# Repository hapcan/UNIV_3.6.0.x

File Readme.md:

UNIV 3.6.0.x
============

Light Dimmer - 1 channel trailing edge light dimmer 250W for DIN rail

Device webpage: http://hapcan.com/devices/universal/univ_3/univ_3-6-0-x/

Hardware designed in Eagle PCB Software http://www.cadsoftusa.com/

Firmware created in Microchip MPLAB http://www.microchip.com/mplabide/ in assembly language

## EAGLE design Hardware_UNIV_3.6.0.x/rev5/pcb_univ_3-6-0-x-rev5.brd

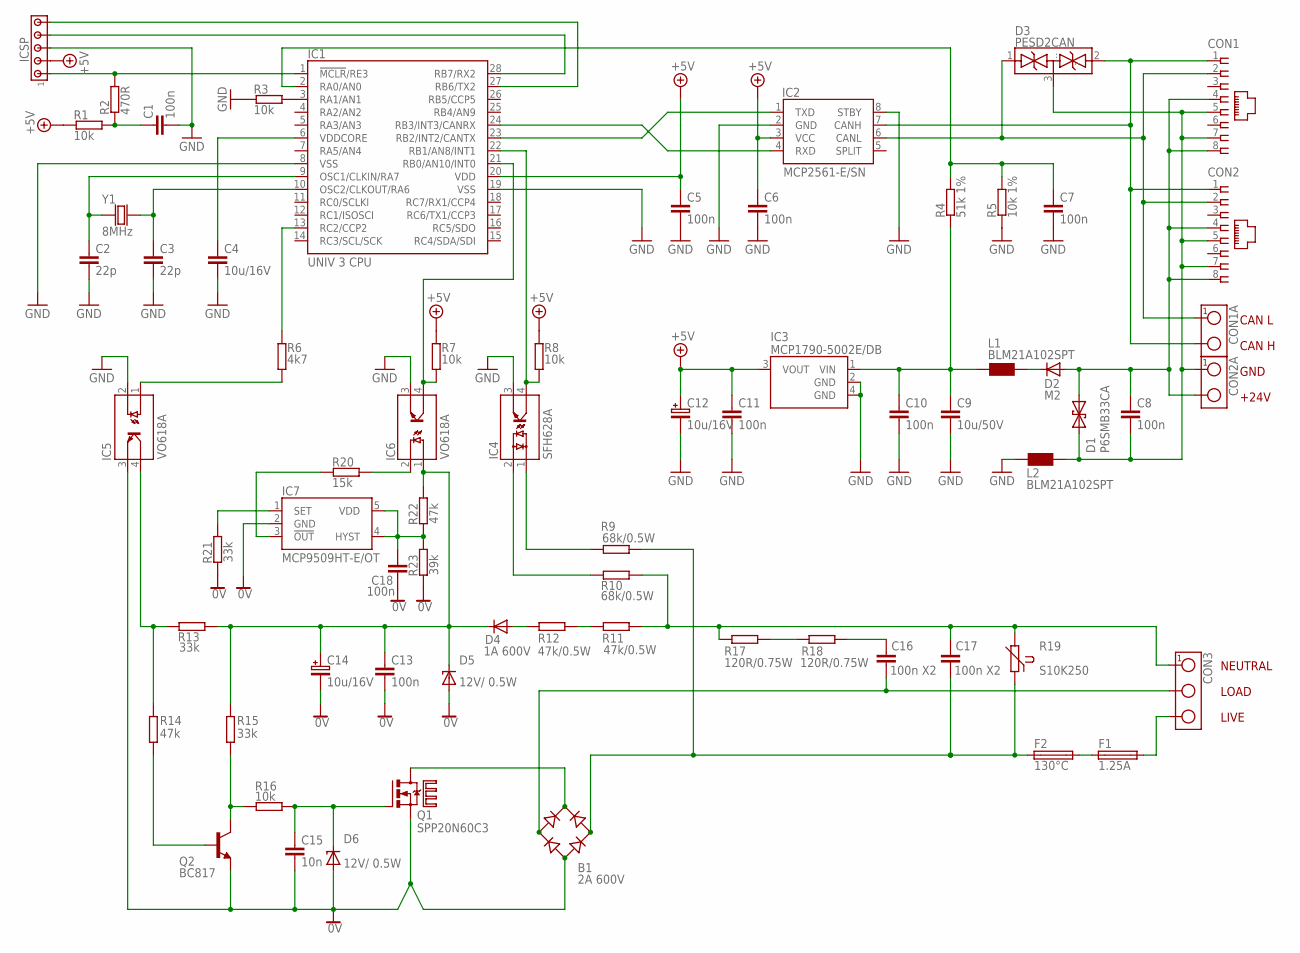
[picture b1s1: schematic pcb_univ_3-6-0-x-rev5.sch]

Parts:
B1: 2A 600V; RECTIFIER_KBP
C1, C5, C6, C7, C8, C10, C11, C13, C18: 100n; 0805
C2, C3: 22p; 0805
C4: 10u/16V; 0805
C9: 10u/50V; 1210
C12, C14: 10u/16V; SMC_B
C15: 10n; 0805
C16, C17: 100n X2; CAP-15X5
CON1, CON2: RJ45-SOCKET; RJ45-PCB-SOCKET
CON1A, CON2A: TERMINAL-2; ARK2-5X10,5MM
CON3: TERMINAL-3; ARK3-5X10.5MM
D1: P6SMB33CA; DO-214_TRANSIL2
D2: M2; DO-214
D3: PESD2CAN; SOT-23
D4: 1A 600V; DO-213
D5, D6: 12V/ 0.5W; SOD-80
F1: 1.25A; FUSE-HOLDER-V
F2: 130°C; FUSE-7.5
IC1: UNIV 3 CPU; UNIV3CPU
IC2: MCP2561-E/SN; SO-08
IC3: MCP1790-5002E/DB; SOT-223
IC4: SFH628A; DIL-04W
IC5, IC6: VO618A; DIL-04W
IC7: MCP9509HT-E/OT; SOT-23-5
ICSP: HEADER5; SIP-5
L1, L2: BLM21A102SPT; 0805
Q1: SPP20N60C3; TO220V-3
Q2: BC817; SOT-23
R1, R3, R7, R8, R16: 10k; 0805
R2: 470R; 0805
R4: 51k 1%; 0805
R5: 10k 1%; 0805
R6: 4k7; 0805
R9, R10: 68k/0.5W; 2010
R11, R12: 47k/0.5W; 2010
R13, R15, R21: 33k; 0805
R14, R22: 47k; 0805
R17, R18: 120R/0.75W; 2010
R19: S10K250; VARISTOR3
R20: 15k; 0805
R23: 39k; 0805
U$1: HEATSINK_HS003; HEATSINK_HS-003
Y1: 8MHz; CRYSTAL-HC49V

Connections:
0V: B1.-, C13.2, C14.- (2), C15.2, C18.2, D5.A, D6.A, IC5.3 (E), IC7.2 (GND), Q1.3 (S), Q2.2 (E), R21.2, R23.2
+5V: C5.1, C6.1, C11.1, C12.+ (1), IC1.20 (VDD), IC2.3 (VCC), IC3.3 (VOUT), ICSP.2, R1.1, R7.2, R8.2
GND: C1.2, C2.2, C3.2, C4.2, C5.2, C6.2, C7.2, C9.2, C10.2, C11.2, C12.- (2), IC1.8 (VSS), IC1.19 (VSS), IC2.2 (GND), IC2.8 (STBY), IC3.2 (GND), IC3.4 (GND), IC4.3 (E1), IC5.2 (K), IC6.3 (E), ICSP.3, L2.1, R3.1, R5.1
unnamed: C13.1, C14.+ (1), D4.C, D5.C, IC6.1 (A), R13.2, R15.1, R22.2
unnamed: IC1.24 (RB3/INT3/CANRX), IC2.4 (RXD)
unnamed: IC1.23 (RB2/INT2/CANTX), IC2.1 (TXD)
unnamed: CON1.1, CON1A.2, CON2.1, D3.2 (..), IC2.7 (CANH)
unnamed: IC4.2 (A2), R10.1
unnamed: B1.+, Q1.2 (D)
unnamed: C1.1, R1.2, R2.1
unnamed: IC1.1 (!MCLR!/RE3), ICSP.1, R2.2
unnamed: C8.1, CON1.4, CON1.8, CON2.4, CON2.8, CON2A.2, D1.C (2), D2.A
unnamed: IC1.28 (RB7/RX2), ICSP.4
unnamed: Q2.3 (C), R15.2, R16.2
unnamed: IC1.3 (RA1/AN1), R3.2
unnamed: B1.AC2, C17.2, F2.1, R9.2, R19.1
unnamed: IC1.27 (RB6/TX2), ICSP.5
unnamed: C3.1, IC1.10 (OSC2/CLKOUT/RA6), Y1.2
unnamed: C7.1, IC1.2 (RA0/AN0), R4.2, R5.2
unnamed: C9.1, C10.1, IC3.1 (VIN), L1.1, R4.1
unnamed: C15.1, D6.C, Q1.1 (G), R16.1
unnamed: IC1.13 (RC2/CCP2), R6.1
unnamed: B1.AC1, C16.1, CON3.2
unnamed: R11.2, R12.1
unnamed: CON3.3, F1.1
unnamed: IC4.1 (A1), R9.1
unnamed: F1.2, F2.2
unnamed: D4.A, R12.2
unnamed: R17.1, R18.2
unnamed: CON1.2, CON1A.1, CON2.2, D3.1 (.), IC2.6 (CANL)
unnamed: C17.1, CON3.1, R10.2, R11.1, R17.2, R19.2
unnamed: C16.2, R18.1
unnamed: IC5.4 (C), R13.1, R14.1
unnamed: Q2.1 (B), R14.2
unnamed: C8.2, CON1.5, CON1.7, CON2.5, CON2.7, CON2A.1, D1.A (1), D3.3 (...), L2.2
unnamed: IC1.21 (RB0/AN10/INT0), IC6.4 (C), R7.1
unnamed: IC7.3 (!OUT), R20.2
unnamed: IC7.1 (SET), R21.1
unnamed: IC1.22 (RB1/AN8/INT1), IC4.4 (C1), R8.1
unnamed: IC5.1 (A), R6.2
unnamed: C18.1, IC7.4 (HYST), IC7.5 (VDD), R22.1, R23.1
unnamed: C2.1, IC1.9 (OSC1/CLKIN/RA7), Y1.1
unnamed: IC6.2 (K), R20.1
unnamed: C4.1, IC1.6 (VDDCORE)
unnamed: D2.C, L1.2

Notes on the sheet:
LOAD
LIVE
NEUTRAL
CAN L
CAN H
GND
+24V

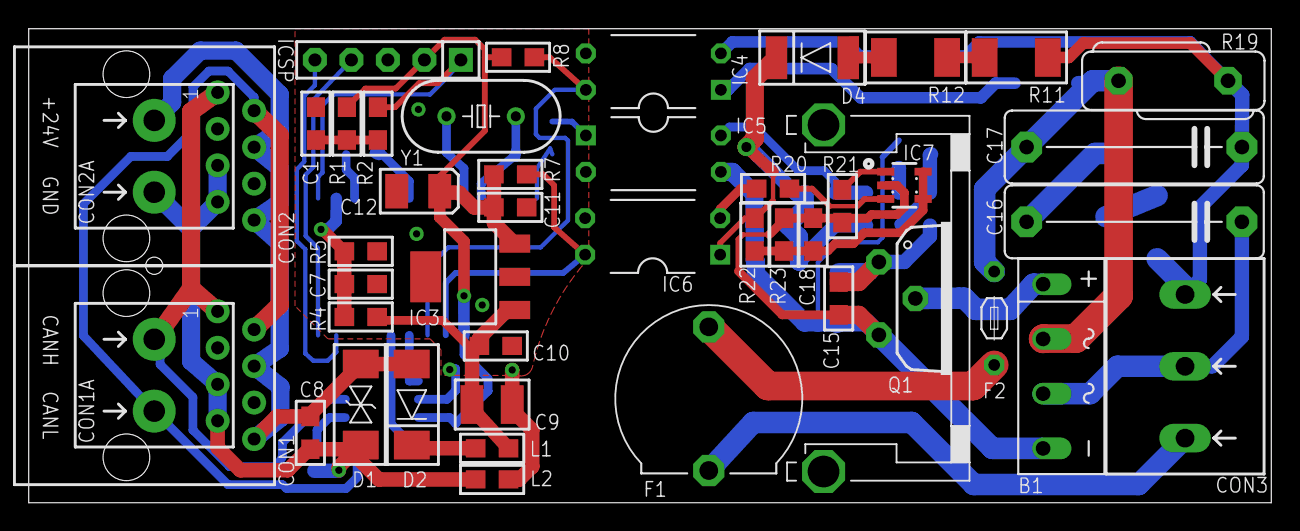
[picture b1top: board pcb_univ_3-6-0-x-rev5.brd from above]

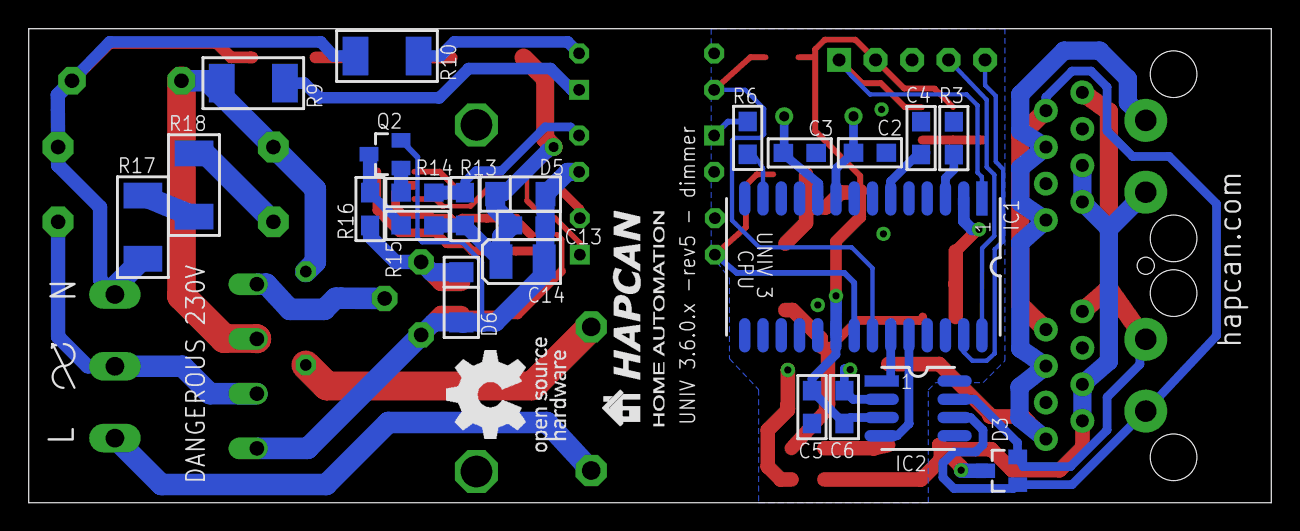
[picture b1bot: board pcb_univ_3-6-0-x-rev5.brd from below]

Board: 2 copper layers, 86.5 x 33.0 mm, 69 parts (23 on the bottom side), 45 nets.

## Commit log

2015-05-31 :space_invader: Added .gitattributes & .gitignore files
2015-05-31 initial commmit
2015-05-31 hardware UNIV 3.6.0.x rev5
2015-06-01 firmware UNIV 3.6.0.1 rev0
2015-09-26 firmware UNIV 3.6.0.1 rev1
2019-02-10 firmware UNIV 3.6.0.2 rev0
2022-11-05 firmware UNIV 3.6.0.2 revision 1
2022-11-05 MIT license
